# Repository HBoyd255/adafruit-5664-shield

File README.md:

# Adafruit 5664 Shield

This is a KiCad library representing the
[Adafruit PCA9546 4-Channel STEMMA QT / Qwiic I2C Multiplexer](https://www.adafruit.com/product/5664),
as a shield.

This allows for a 4 Channel Qwiic I2C Multiplexer to be added to a PCB, without
the need for surface mount soldering.

## Images

Here is what the footprint looks like in KiCad:

### Footprint

### Silkscreen

### 3D Model

## Setup

To get the library working, you need to add path of this repository to the KiCad
library search path. This can be done by going to
`Preferences -> Configure Paths` and adding the path with the name
`Adafruit_5664_Shield`.

## License

This footprint is derived from the original board by Adafruit, used under CC
BY-SA 3.0. This library is also licensed under CC BY-SA 3.0.

The original board can be found at:
[github.com/adafruit/Adafruit-PCA9546-PCB](https://github.com/adafruit/Adafruit-PCA9546-PCB).

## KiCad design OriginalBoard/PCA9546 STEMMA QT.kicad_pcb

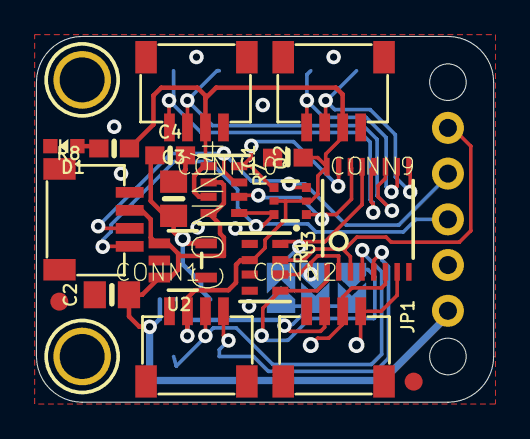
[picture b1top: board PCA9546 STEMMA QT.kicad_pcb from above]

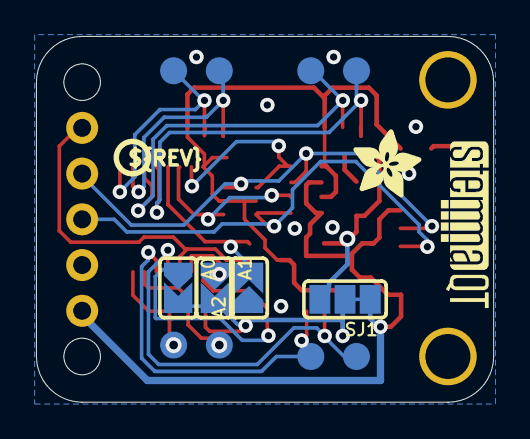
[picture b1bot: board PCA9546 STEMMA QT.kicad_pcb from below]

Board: 2 copper layers, 25.4 x 20.3 mm, 57 parts (24 on the bottom side), 21 nets.

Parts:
@HOLE0, @HOLE1: (no value)
A0, A1, A2: SOLDERJUMPER_ARROW_NOPASTE
C1: 1uF; 0603-NO
C2, C3: 10uF; 0805-NO
C4: 0.1uF; 0603-NO
CONN1, CONN2, CONN4, CONN9, CONN10: STEMMA_I2C_QT; JST_SH4
D1: GREEN; CHIPLED_0603_NOOUTLINE
FID2, FID4: FIDUCIAL_1MM
JP1: 1X05_ROUND_70
PLABEL0: PLABEL0
PLABEL1: PLABEL1
PLABEL2: PLABEL2
PLABEL3: PLABEL3
PLABEL4: PLABEL4
PLABEL5: PLABEL5
PLABEL6: PLABEL6
PLABEL7: PLABEL7
PLABEL8: PLABEL8
PLABEL9: PLABEL9
PLABEL10: PLABEL10
PLABEL11: PLABEL11
PLABEL12: PLABEL12
PLABEL13: PLABEL13
PLABEL14: PLABEL14
PLABEL15: PLABEL15
PLABEL16: PLABEL16
PLABEL17: PLABEL17
PLABEL18: PLABEL18
Q2: BSS138; SOT363
R1, R7: 10K Pack; RESPACK_4X0603
R8: 10K; 0603-NO
SJ1: SOLDERJUMPER_2WAY_OPEN_NOPASTE
TP1, TP2, TP3, TP4, TP5, TP6, TP7, TP8: TESTPOINT_ROUND_1.5MM_NO
U2: AP2112K-3.3; SOT23-5
U3: PCA9546 TSSOP; TSSOP16
U$19, U$22: MOUNTINGHOLE2.5; MOUNTINGHOLE_2.5_PLATED
U$28: ADAFRUIT_3.5MM
U$29: PCBFEAT-REV-040
U$31: STEMMAQT

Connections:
0SCL: CONN1.4, TP2.P$1, U3.5
0SDA: CONN1.3, TP1.P$1, U3.4
1SCL: CONN2.4, TP4.P$1, U3.7
1SDA: CONN2.3, TP3.P$1, U3.6
2SCL: CONN9.4, TP6.P$1, U3.10
2SDA: CONN9.3, TP5.P$1, U3.9
3.3V: C3.1, C4.1, SJ1.3, U2.5
3SCL: CONN10.4, TP8.P$1, U3.12
3SDA: CONN10.3, TP7.P$1, U3.11
A0: A0.1, R1.5, U3.1
A1: A1.1, R1.6, U3.2
A2: A2.2, R1.8, U3.13
GND: C1.2, C2.2, C3.2, C4.2, CONN1.1, CONN1.MT1, CONN1.MT2, CONN2.1, CONN2.MT1, CONN2.MT2, CONN4.1, CONN4.MT1, CONN4.MT2, CONN9.1, CONN9.MT1, CONN9.MT2, CONN10.1, CONN10.MT1, CONN10.MT2, D1.C, JP1.2, R1.1, R1.3, R1.4, U2.2, U3.8
unnamed: D1.A, R8.2
RESET: JP1.5, R1.7, U3.3
SCL: CONN4.4, JP1.3, Q2.6, R7.5
SCL_IO: Q2.1, R7.6, U3.14
SDA: CONN4.3, JP1.4, Q2.3, R7.7
SDA_IO: Q2.4, R7.8, U3.15
VCC: C2.1, CONN4.2, JP1.1, R7.2, R7.4, SJ1.1, U2.1, U2.3
VCCIO: A0.2, A1.2, A2.1, C1.1, CONN1.2, CONN2.2, CONN9.2, CONN10.2, Q2.2, Q2.5, R1.2, R7.1, R7.3, R8.1, SJ1.2, U3.16

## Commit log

2024-07-23 Created repo
2024-07-23 Imported existing board
2024-07-23 Grouped edge cuts
2024-07-28 Added 3D models
2024-07-28 Added detail to silkscreen
2024-07-28 Added images
2024-07-28 Updated reference to 3d model
2024-08-15 Removed duplicate holes
